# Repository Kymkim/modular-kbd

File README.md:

# MSKBD - Modularly Simple KeyBoarD

> [!WARNING]  
> This is under development. If you want the latest developments check out the `dev` branch.

A customizable modular keyboard system where each key cluster is its own module, connected through a grid-like commnication. The goal is to create a flexible keyboard that can scale, reconfigure layouts, and support hot-swapping modules.

## Features
- 🧩 **Modular design** — attach modules in any direction
- 🎛️ **Configurable firmware** — master + module code, easily updated
- ⚡ **Hotplug detection** — modules can be discovered dynamically

# Numpad Module

## Repo Structure
```
├─firmware/ - Embedded code for the core system
├─hardware/ - Schematics and PCB layouts
├─software/ - Host tools (keymap editor, etc.) (not yet implemented - soon hopefully!)
├─docs/ - Design notes, communication protocol, build guides
└─assets/ - Renders, diagrams, and media
```

## Branch Structure
```
main              # Stable, production-ready code (only tested & reviewed changes go here)
│
├─ dev            # Integration branch for features; "staging" area before merging to main
│  ├─ software-xxxxxx     # New features, experiments, improvements, or PCB uploads    
|  ├─ firmware-xxxxxx     # Please indicate in the branch the wether if its software
│  └─ hardware-xxxxxx     # firmware, or hardware
│
├─ hotfix/        # Quick fixes for urgent bugs in main
│   └─ hotfix/usb-detection
│
└─ docs/          # Documentation updates
    └─ docs/protocol-update
```

## Contributors

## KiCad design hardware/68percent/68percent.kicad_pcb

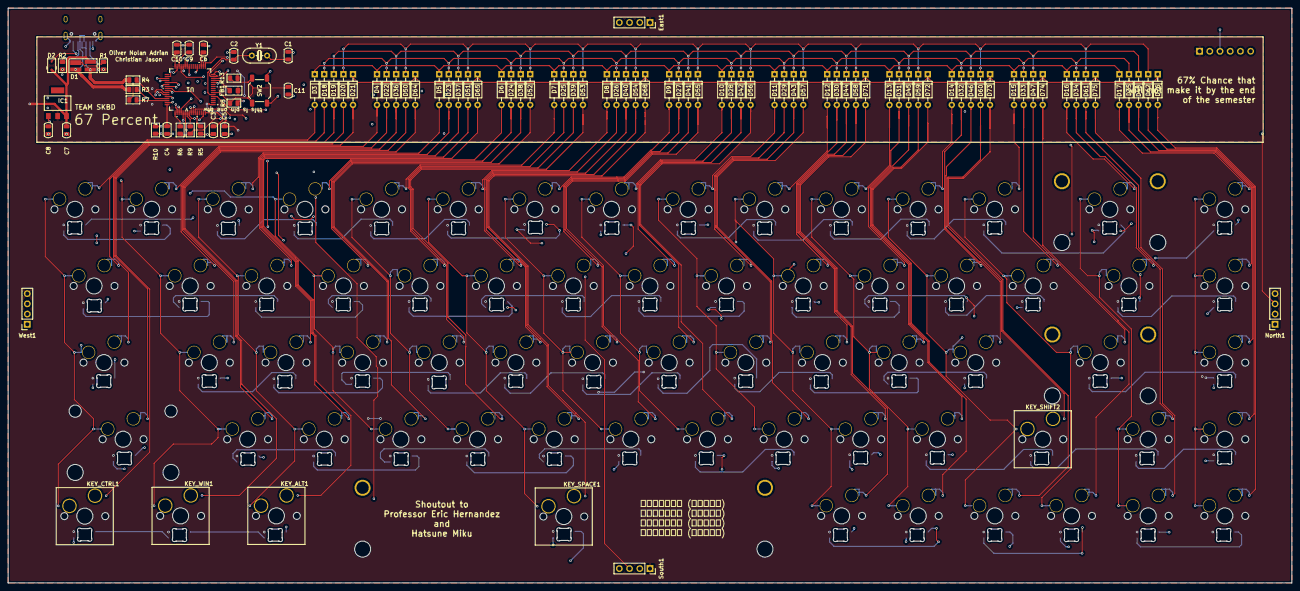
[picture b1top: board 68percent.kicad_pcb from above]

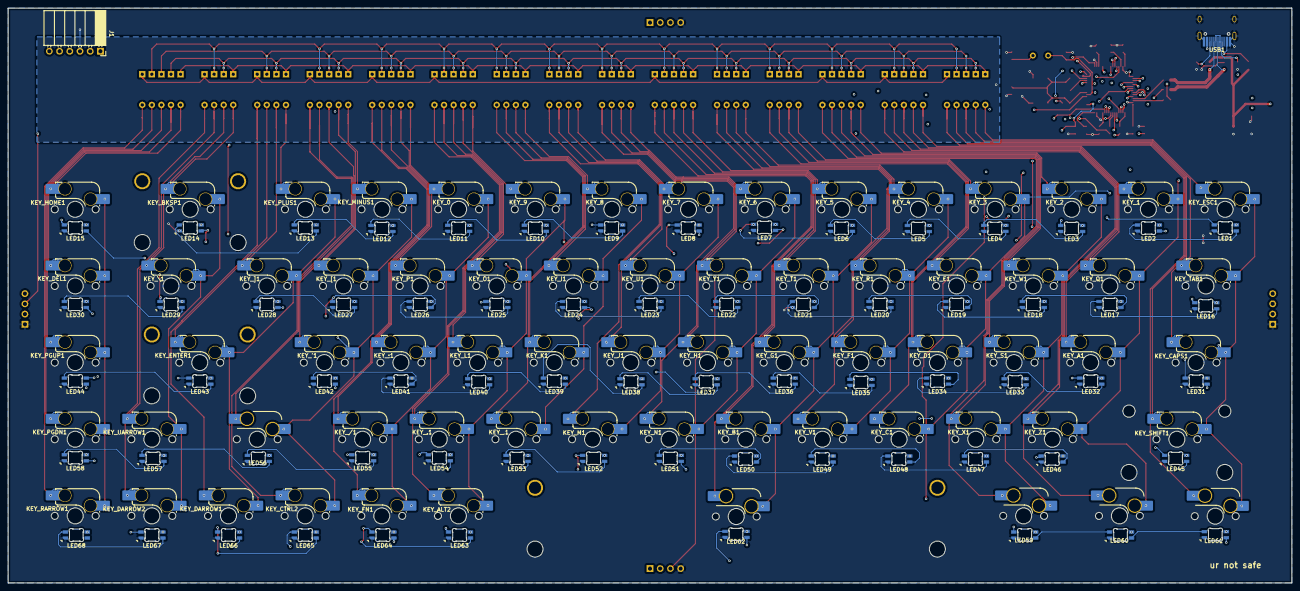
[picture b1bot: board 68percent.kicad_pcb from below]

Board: 4 copper layers, 319.1 x 142.9 mm, 243 parts (133 on the bottom side), 188 nets.

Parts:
C1, C2: 20pF; C_0805_2012Metric
C3, C4, C5, C6: 100nF; C_0805_2012Metric
C7, C10: 1uF; C_0805_2012Metric
C8: 10uF; C_0805_2012Metric
C9: 4.7uF; C_0805_2012Metric
C11: 0.1uF; C_0805_2012Metric
D1: PRTR5V0U2X; SOT-143_Handsoldering
D2: BAT60JFILM; D_SOD-323
D3, D4, D5, D6, D7, D8, D9, D10, D11, D12, D13, D14, D15, D16, D17, D18, D19, D20, D21, D22, D23, D24, D25, D26, D27, D28, D29, D30, D31, D32, D33, D34, D35, D36, D37, D38, D39, D40, D41, D42, D43, D44, D45, D46, D47, D48, D50, D51, D52, D53, D54, D55, D56, D57, D58, D59, D60, D61, D62, D64, D65, D68, D71, D72, D73, D74, D75, D76: 1N4148W; D_DO-35_P7.62mm_Horizontal
East1: Conn_01x04; PinSocket_1x04_P2.54mm_Vertical
FB1: Ferrite_Bead; Fuse_0805_2012Metric_Pad1.15x1.40mm_BigPads
IC1: TEAM SKBD; SOT223
J1: Conn_01x06; PinSocket_1x06_P2.54mm_Horizontal
KEY_0, KEY_1, KEY_2, KEY_3, KEY_4, KEY_5, KEY_6, KEY_7, KEY_8, KEY_9, KEY_.1: MX_SW_HS; SW_MX_HS_CPG151101S11_1u
KEY_'1: MX_SW_HS; SW_MX_HS_CPG151101S11_1u
KEY_,1: MX_SW_HS; SW_MX_HS_CPG151101S11_1u
KEY_/1: MX_SW_HS; SW_MX_HS_CPG151101S11_1u
KEY_;1: MX_SW_HS; SW_MX_HS_CPG151101S11_1u
KEY_A1: MX_SW_HS; SW_MX_HS_CPG151101S11_1u
KEY_ALT1: MX_SW_HS; SW_Hotswap_Kailh_MX_Plated_1.25u
KEY_ALT2: MX_SW_HS; SW_MX_HS_CPG151101S11_1u
KEY_B1: MX_SW_HS; SW_MX_HS_CPG151101S11_1u
KEY_BKSP1: MX_SW_HS; SW_MX_HS_CPG151101S11_1u
KEY_C1: MX_SW_HS; SW_MX_HS_CPG151101S11_1u
KEY_CAPS1: MX_SW_HS; SW_MX_HS_CPG151101S11_1u
KEY_CTRL1: MX_SW_HS; SW_Hotswap_Kailh_MX_Plated_1.25u
KEY_CTRL2: MX_SW_HS; SW_MX_HS_CPG151101S11_1u
KEY_D1: MX_SW_HS; SW_MX_HS_CPG151101S11_1u
KEY_DARROW1, KEY_DARROW2: MX_SW_HS; SW_MX_HS_CPG151101S11_1u
KEY_DEL1: MX_SW_HS; SW_MX_HS_CPG151101S11_1u
KEY_E1: MX_SW_HS; SW_MX_HS_CPG151101S11_1u
KEY_ENTER1: MX_SW_HS; SW_MX_HS_CPG151101S11_1u
KEY_ESC1: MX_SW_HS; SW_MX_HS_CPG151101S11_1u
KEY_F1: MX_SW_HS; SW_MX_HS_CPG151101S11_1u
KEY_FN1: MX_SW_HS; SW_MX_HS_CPG151101S11_1u
KEY_G1: MX_SW_HS; SW_MX_HS_CPG151101S11_1u
KEY_H1: MX_SW_HS; SW_MX_HS_CPG151101S11_1u
KEY_HOME1: MX_SW_HS; SW_MX_HS_CPG151101S11_1u
KEY_I1: MX_SW_HS; SW_MX_HS_CPG151101S11_1u
KEY_J1: MX_SW_HS; SW_MX_HS_CPG151101S11_1u
KEY_K1: MX_SW_HS; SW_MX_HS_CPG151101S11_1u
KEY_L1: MX_SW_HS; SW_MX_HS_CPG151101S11_1u
KEY_M1: MX_SW_HS; SW_MX_HS_CPG151101S11_1u
KEY_MINUS1: MX_SW_HS; SW_MX_HS_CPG151101S11_1u
KEY_N1: MX_SW_HS; SW_MX_HS_CPG151101S11_1u
KEY_O1: MX_SW_HS; SW_MX_HS_CPG151101S11_1u
KEY_P1: MX_SW_HS; SW_MX_HS_CPG151101S11_1u
KEY_PGDN1: MX_SW_HS; SW_MX_HS_CPG151101S11_1u
KEY_PGUP1: MX_SW_HS; SW_MX_HS_CPG151101S11_1u
KEY_PLUS1: MX_SW_HS; SW_MX_HS_CPG151101S11_1u
KEY_Q1: MX_SW_HS; SW_MX_HS_CPG151101S11_1u
KEY_R1: MX_SW_HS; SW_MX_HS_CPG151101S11_1u
KEY_RARROW1: MX_SW_HS; SW_MX_HS_CPG151101S11_1u
KEY_S1: MX_SW_HS; SW_MX_HS_CPG151101S11_1u
KEY_SHIFT1: MX_SW_HS; SW_MX_HS_CPG151101S11_1u
KEY_SHIFT2: MX_SW_HS; SW_Hotswap_Kailh_MX_Plated_1.75u
KEY_SPACE1: MX_SW_HS; SW_Hotswap_Kailh_MX_Plated_1.25u
KEY_T1: MX_SW_HS; SW_MX_HS_CPG151101S11_1u
KEY_TAB1: MX_SW_HS; SW_MX_HS_CPG151101S11_1u
KEY_U1: MX_SW_HS; SW_MX_HS_CPG151101S11_1u
KEY_UARROW1: MX_SW_HS; SW_MX_HS_CPG151101S11_1u
KEY_V1: MX_SW_HS; SW_MX_HS_CPG151101S11_1u
KEY_W1: MX_SW_HS; SW_MX_HS_CPG151101S11_1u
KEY_WIN1: MX_SW_HS; SW_Hotswap_Kailh_MX_Plated_1.25u
KEY_X1: MX_SW_HS; SW_MX_HS_CPG151101S11_1u
KEY_Y1: MX_SW_HS; SW_MX_HS_CPG151101S11_1u
KEY_Z1: MX_SW_HS; SW_MX_HS_CPG151101S11_1u
KEY_[1: MX_SW_HS; SW_MX_HS_CPG151101S11_1u
KEY_\1: MX_SW_HS; SW_MX_HS_CPG151101S11_1.5u
KEY_]1: MX_SW_HS; SW_MX_HS_CPG151101S11_1u
LED1, LED2, LED3, LED4, LED5, LED6, LED7, LED8, LED9, LED10, LED11, LED12, LED13, LED14, LED15, LED16, LED17, LED18, LED19, LED20, LED21, LED22, LED23, LED24, LED25, LED26, LED27, LED28, LED29, LED30, LED31, LED32, LED33, LED34, LED35, LED36, LED37, LED38, LED39, LED40, LED41, LED42, LED43, LED44, LED45, LED46, LED47, LED48, LED49, LED50, LED51, LED52, LED53, LED54, LED55, LED56, LED57, LED58, LED59, LED60, LED61, LED62, LED63, LED64, LED65, LED66, LED67, LED68: choc_SK6812MINI-E; LED_choc_6028R
North1: Conn_01x04; PinSocket_1x04_P2.54mm_Vertical
R1, R2: 5.1k; R_0805_2012Metric
R3, R4, R6, R7, R8, R9: 22; R_0805_2012Metric
R5: 10k; R_0805_2012Metric
R10, R13: DNP; R_0805_2012Metric
S1: MX_stab; STAB_MX_2.25u
S2: MX_stab; STAB_MX_P_6.25u
S3: MX_stab; STAB_MX_P_2u
S4: MX_stab; STAB_MX_P_2.25u
SW2: Push_Button; SW_SPST_SKQG_WithStem
South1: Conn_01x04; PinSocket_1x04_P2.54mm_Vertical
U1: LQFP64-10x10mm
USB1: HRO-TYPE-C-31-M-12; HRO-TYPE-C-31-M-12-HandSoldering
West1: Conn_01x04; PinSocket_1x04_P2.54mm_Vertical
Y1: 8MHz; Crystal_HC52-U_Vertical

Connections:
+3.3V: C3.1, C4.1, C5.1, C6.1, C8.2, C10.1, FB1.2, IC1.2 (OUT), J1.1, R13.2, U1.1 (VBAT), U1.19 (VDD), U1.32 (VDD), U1.48 (VDD), U1.64 (VDD)
+5V: C7.1, D1.4 (VP), D2.1 (K), East1.1, IC1.3 (IN), LED1.1 (VDD), LED2.1 (VDD), LED3.1 (VDD), LED4.1 (VDD), LED5.1 (VDD), LED6.1 (VDD), LED7.1 (VDD), LED8.1 (VDD), LED9.1 (VDD), LED10.1 (VDD), LED11.1 (VDD), LED12.1 (VDD), LED13.1 (VDD), LED14.1 (VDD), LED15.1 (VDD), LED16.1 (VDD), LED17.1 (VDD), LED18.1 (VDD), LED19.1 (VDD), LED20.1 (VDD), LED21.1 (VDD), LED22.1 (VDD), LED23.1 (VDD), LED24.1 (VDD), LED25.1 (VDD), LED26.1 (VDD), LED27.1 (VDD), LED28.1 (VDD), LED29.1 (VDD), LED30.1 (VDD), LED31.1 (VDD), LED32.1 (VDD), LED33.1 (VDD), LED34.1 (VDD), LED35.1 (VDD), LED36.1 (VDD), LED37.1 (VDD), LED38.1 (VDD), LED39.1 (VDD), LED40.1 (VDD), LED41.1 (VDD), LED42.1 (VDD), LED43.1 (VDD), LED44.1 (VDD), LED45.1 (VDD), LED46.1 (VDD), LED47.1 (VDD), LED48.1 (VDD), LED49.1 (VDD), LED50.1 (VDD), LED51.1 (VDD), LED52.1 (VDD), LED53.1 (VDD), LED54.1 (VDD), LED55.1 (VDD), LED56.1 (VDD), LED57.1 (VDD), LED58.1 (VDD), LED59.1 (VDD), LED60.1 (VDD), LED61.1 (VDD), LED62.1 (VDD), LED63.1 (VDD), LED64.1 (VDD), LED65.1 (VDD), LED66.1 (VDD), LED67.1 (VDD), LED68.1 (VDD), North1.4, South1.1, West1.4
/COL1: KEY_CAPS1.1, KEY_CTRL1.1, KEY_ESC1.1, KEY_SHIFT1.1, KEY_TAB1.1, U1.34 (PB13)
/COL2: KEY_1.1, KEY_A1.1, KEY_Q1.1, KEY_WIN1.1, KEY_Z1.1, U1.35 (PB14)
/COL3: KEY_2.1, KEY_ALT1.1, KEY_S1.1, KEY_W1.1, KEY_X1.1, U1.36 (PB15)
/COL4: KEY_3.1, KEY_C1.1, KEY_D1.1, KEY_E1.1, U1.37 (PC6)
/COL5: KEY_4.1, KEY_F1.1, KEY_R1.1, KEY_V1.1, U1.38 (PC7)
/COL6: KEY_5.1, KEY_B1.1, KEY_G1.1, KEY_SPACE1.1, KEY_T1.1, U1.39 (PC8)
/COL7: KEY_6.1, KEY_H1.1, KEY_N1.1, KEY_Y1.1, U1.40 (PC9)
/COL8: KEY_7.1, KEY_J1.1, KEY_M1.1, KEY_U1.1, U1.41 (PA8)
/COL9: KEY_8.1, KEY_,1.1, KEY_I1.1, KEY_K1.1, U1.50 (PA15)
/COL10: KEY_9.1, KEY_.1.1, KEY_ALT2.1, KEY_L1.1, KEY_O1.1, U1.51 (PA10)
/COL11: KEY_0.1, KEY_/1.1, KEY_;1.1, KEY_FN1.1, KEY_P1.1, U1.52 (PC11)
/COL12: KEY_'1.1, KEY_CTRL2.1, KEY_MINUS1.1, KEY_SHIFT2.1, KEY_[1.1, U1.56 (PB4)
/COL13: KEY_DARROW1.1, KEY_ENTER1.1, KEY_PLUS1.1, KEY_]1.1, U1.57 (PB5)
/COL14: KEY_BKSP1.1, KEY_DARROW2.1, KEY_UARROW1.1, KEY_\1.1, U1.58 (PB6)
/COL15: KEY_DEL1.1, KEY_HOME1.1, KEY_PGDN1.1, KEY_PGUP1.1, KEY_RARROW1.1, U1.59 (PB7)
/D+: D1.3 (L2), R4.1, USB1.6 (DP1), USB1.8 (DP2)
/D-: D1.2 (L1), R3.2, USB1.5 (DN2), USB1.7 (DN1)
/JTCLK: R6.2, U1.49 (PA14)
/JTMS: R7.2, U1.46 (PA13)
/NRST: C11.2, R8.1, R13.1, SW2.1, U1.7 (NRST)
/RGB_DATAIN: LED1.3 (DIN), U1.21 (PA5)
/ROW1: D3.1 (K), D4.1 (K), D5.1 (K), D6.1 (K), D7.1 (K), D8.1 (K), D9.1 (K), D10.1 (K), D11.1 (K), D12.1 (K), D13.1 (K), D14.1 (K), D15.1 (K), D16.1 (K), D17.1 (K), U1.29 (PB10)
/ROW2: D18.1 (K), D22.1 (K), D23.1 (K), D24.1 (K), D25.1 (K), D26.1 (K), D27.1 (K), D28.1 (K), D29.1 (K), D30.1 (K), D31.1 (K), D32.1 (K), D33.1 (K), D34.1 (K), D35.1 (K), U1.28 (PB2)
/ROW3: D19.1 (K), D36.1 (K), D37.1 (K), D38.1 (K), D39.1 (K), D40.1 (K), D41.1 (K), D42.1 (K), D43.1 (K), D44.1 (K), D45.1 (K), D46.1 (K), D47.1 (K), D48.1 (K), U1.27 (PB1)
/ROW4: D20.1 (K), D50.1 (K), D51.1 (K), D52.1 (K), D53.1 (K), D54.1 (K), D55.1 (K), D56.1 (K), D57.1 (K), D58.1 (K), D59.1 (K), D60.1 (K), D61.1 (K), D62.1 (K), U1.26 (PB0)
/ROW5: D21.1 (K), D64.1 (K), D65.1 (K), D68.1 (K), D71.1 (K), D72.1 (K), D73.1 (K), D74.1 (K), D75.1 (K), D76.1 (K), U1.25 (PC5)
/SWO: R9.2, U1.55 (PB3)
/UART_RX_EAST: East1.2, U1.14 (PA0)
/UART_RX_NORTH: North1.2, U1.17 (PA3)
/UART_RX_SOUTH: South1.2, U1.54 (PD2)
/UART_RX_WEST: U1.42 (PA9), West1.2
/UART_TX_EAST: East1.3, U1.15 (PA1)
/UART_TX_NORTH: North1.3, U1.16 (PA2)
/UART_TX_SOUTH: South1.3, U1.53 (PC12)
/UART_TX_WEST: U1.43 (PA10), West1.3
AGND: R10.1, U1.12 (VSSA)
GND: C1.2, C2.2, C3.2, C4.2, C5.2, C6.2, C7.2, C8.1, C9.1, C10.2, C11.1, D1.1 (VN), East1.4, IC1.1 (ADJ), J1.3, LED1.4 (VSS), LED2.4 (VSS), LED3.4 (VSS), LED4.4 (VSS), LED5.4 (VSS), LED6.4 (VSS), LED7.4 (VSS), LED8.4 (VSS), LED9.4 (VSS), LED10.4 (VSS), LED11.4 (VSS), LED12.4 (VSS), LED13.4 (VSS), LED14.4 (VSS), LED15.4 (VSS), LED16.4 (VSS), LED17.4 (VSS), LED18.4 (VSS), LED19.4 (VSS), LED20.4 (VSS), LED21.4 (VSS), LED22.4 (VSS), LED23.4 (VSS), LED24.4 (VSS), LED25.4 (VSS), LED26.4 (VSS), LED27.4 (VSS), LED28.4 (VSS), LED29.4 (VSS), LED30.4 (VSS), LED31.4 (VSS), LED32.4 (VSS), LED33.4 (VSS), LED34.4 (VSS), LED35.4 (VSS), LED36.4 (VSS), LED37.4 (VSS), LED38.4 (VSS), LED39.4 (VSS), LED40.4 (VSS), LED41.4 (VSS), LED42.4 (VSS), LED43.4 (VSS), LED44.4 (VSS), LED45.4 (VSS), LED46.4 (VSS), LED47.4 (VSS), LED48.4 (VSS), LED49.4 (VSS), LED50.4 (VSS), LED51.4 (VSS), LED52.4 (VSS), LED53.4 (VSS), LED54.4 (VSS), LED55.4 (VSS), LED56.4 (VSS), LED57.4 (VSS), LED58.4 (VSS), LED59.4 (VSS), LED60.4 (VSS), LED61.4 (VSS), LED62.4 (VSS), LED63.4 (VSS), LED64.4 (VSS), LED65.4 (VSS), LED66.4 (VSS), LED67.4 (VSS), LED68.4 (VSS), North1.1, R1.2, R2.2, R5.1, R10.2, SW2.2, South1.4, U1.18 (VSS), U1.31 (VSS), U1.47 (VSS), U1.63 (VSS), USB1.1 (GND), USB1.12 (GND), USB1.13 (SHIELD), West1.1
unnamed: D2.2 (A), USB1.2 (VBUS), USB1.11 (VBUS)
unnamed: D3.2 (A), KEY_ESC1.2
unnamed: D4.2 (A), KEY_1.2
unnamed: D5.2 (A), KEY_2.2
unnamed: D6.2 (A), KEY_3.2
unnamed: D7.2 (A), KEY_4.2
unnamed: D8.2 (A), KEY_5.2
unnamed: D9.2 (A), KEY_6.2
unnamed: D10.2 (A), KEY_7.2
unnamed: D11.2 (A), KEY_8.2
unnamed: D12.2 (A), KEY_9.2
unnamed: D13.2 (A), KEY_0.2
unnamed: D14.2 (A), KEY_MINUS1.2
unnamed: D15.2 (A), KEY_PLUS1.2
unnamed: D16.2 (A), KEY_BKSP1.2
unnamed: D17.2 (A), KEY_HOME1.2
unnamed: D18.2 (A), KEY_TAB1.2
unnamed: D19.2 (A), KEY_CAPS1.2
unnamed: D20.2 (A), KEY_SHIFT1.2
unnamed: D21.2 (A), KEY_CTRL1.2
unnamed: D22.2 (A), KEY_Q1.2
unnamed: D23.2 (A), KEY_W1.2
unnamed: D24.2 (A), KEY_E1.2
unnamed: D25.2 (A), KEY_R1.2
unnamed: D26.2 (A), KEY_T1.2
unnamed: D27.2 (A), KEY_Y1.2
unnamed: D28.2 (A), KEY_U1.2
unnamed: D29.2 (A), KEY_I1.2
unnamed: D30.2 (A), KEY_O1.2
unnamed: D31.2 (A), KEY_P1.2
unnamed: D32.2 (A), KEY_[1.2
unnamed: D33.2 (A), KEY_]1.2
unnamed: D34.2 (A), KEY_\1.2
unnamed: D35.2 (A), KEY_DEL1.2
unnamed: D36.2 (A), KEY_A1.2
unnamed: D37.2 (A), KEY_S1.2
unnamed: D38.2 (A), KEY_D1.2
unnamed: D39.2 (A), KEY_F1.2
unnamed: D40.2 (A), KEY_G1.2
unnamed: D41.2 (A), KEY_H1.2
unnamed: D42.2 (A), KEY_J1.2
unnamed: D43.2 (A), KEY_K1.2
unnamed: D44.2 (A), KEY_L1.2
unnamed: D45.2 (A), KEY_;1.2
unnamed: D46.2 (A), KEY_'1.2
unnamed: D47.2 (A), KEY_ENTER1.2
unnamed: D48.2 (A), KEY_PGUP1.2
unnamed: D50.2 (A), KEY_Z1.2
unnamed: D51.2 (A), KEY_X1.2
unnamed: D52.2 (A), KEY_C1.2
unnamed: D53.2 (A), KEY_V1.2
unnamed: D54.2 (A), KEY_B1.2
unnamed: D55.2 (A), KEY_N1.2
unnamed: D56.2 (A), KEY_M1.2
unnamed: D57.2 (A), KEY_,1.2
unnamed: D58.2 (A), KEY_.1.2
unnamed: D59.2 (A), KEY_/1.2
unnamed: D60.2 (A), KEY_SHIFT2.2
unnamed: D61.2 (A), KEY_UARROW1.2
unnamed: D62.2 (A), KEY_PGDN1.2
unnamed: D64.2 (A), KEY_WIN1.2
unnamed: D65.2 (A), KEY_ALT1.2
unnamed: D68.2 (A), KEY_SPACE1.2
unnamed: D71.2 (A), KEY_ALT2.2
unnamed: D72.2 (A), KEY_FN1.2
unnamed: D73.2 (A), KEY_CTRL2.2
unnamed: D74.2 (A), KEY_DARROW1.2
unnamed: D75.2 (A), KEY_DARROW2.2
unnamed: D76.2 (A), KEY_RARROW1.2
unnamed: J1.2, R6.1
unnamed: J1.4, R7.1
unnamed: J1.5, R8.2
unnamed: J1.6, R9.1
unnamed: LED1.2 (DOUT), LED2.3 (DIN)
unnamed: LED2.2 (DOUT), LED3.3 (DIN)
unnamed: LED3.2 (DOUT), LED4.3 (DIN)
unnamed: LED4.2 (DOUT), LED5.3 (DIN)
unnamed: LED5.2 (DOUT), LED6.3 (DIN)
unnamed: LED6.2 (DOUT), LED7.3 (DIN)
unnamed: LED7.2 (DOUT), LED8.3 (DIN)
unnamed: LED8.2 (DOUT), LED9.3 (DIN)
unnamed: LED9.2 (DOUT), LED10.3 (DIN)
unnamed: LED10.2 (DOUT), LED11.3 (DIN)
unnamed: LED11.2 (DOUT), LED12.3 (DIN)
unnamed: LED12.2 (DOUT), LED13.3 (DIN)
unnamed: LED13.2 (DOUT), LED14.3 (DIN)
unnamed: LED14.2 (DOUT), LED15.3 (DIN)
unnamed: LED15.2 (DOUT), LED16.3 (DIN)
unnamed: LED16.2 (DOUT), LED17.3 (DIN)
unnamed: LED17.2 (DOUT), LED18.3 (DIN)
unnamed: LED18.2 (DOUT), LED19.3 (DIN)
unnamed: LED19.2 (DOUT), LED20.3 (DIN)
unnamed: LED20.2 (DOUT), LED21.3 (DIN)
unnamed: LED21.2 (DOUT), LED22.3 (DIN)
unnamed: LED22.2 (DOUT), LED23.3 (DIN)
unnamed: LED23.2 (DOUT), LED24.3 (DIN)
unnamed: LED24.2 (DOUT), LED25.3 (DIN)
unnamed: LED25.2 (DOUT), LED26.3 (DIN)
unnamed: LED26.2 (DOUT), LED27.3 (DIN)
unnamed: LED27.2 (DOUT), LED28.3 (DIN)
unnamed: LED28.2 (DOUT), LED29.3 (DIN)
unnamed: LED29.2 (DOUT), LED30.3 (DIN)
unnamed: LED30.2 (DOUT), LED31.3 (DIN)
unnamed: LED31.2 (DOUT), LED32.3 (DIN)
unnamed: LED32.2 (DOUT), LED33.3 (DIN)
unnamed: LED33.2 (DOUT), LED34.3 (DIN)
unnamed: LED34.2 (DOUT), LED35.3 (DIN)
unnamed: LED35.2 (DOUT), LED36.3 (DIN)
unnamed: LED36.2 (DOUT), LED37.3 (DIN)
unnamed: LED37.2 (DOUT), LED38.3 (DIN)
unnamed: LED38.2 (DOUT), LED39.3 (DIN)
unnamed: LED39.2 (DOUT), LED40.3 (DIN)
unnamed: LED40.2 (DOUT), LED41.3 (DIN)
unnamed: LED41.2 (DOUT), LED42.3 (DIN)
unnamed: LED42.2 (DOUT), LED43.3 (DIN)
unnamed: LED43.2 (DOUT), LED44.3 (DIN)
unnamed: LED44.2 (DOUT), LED45.3 (DIN)
unnamed: LED45.2 (DOUT), LED46.3 (DIN)
unnamed: LED46.2 (DOUT), LED47.3 (DIN)
unnamed: LED47.2 (DOUT), LED48.3 (DIN)
unnamed: LED48.2 (DOUT), LED49.3 (DIN)
unnamed: LED49.2 (DOUT), LED50.3 (DIN)
unnamed: LED50.2 (DOUT), LED51.3 (DIN)
unnamed: LED51.2 (DOUT), LED52.3 (DIN)
unnamed: LED52.2 (DOUT), LED53.3 (DIN)
unnamed: LED53.2 (DOUT), LED54.3 (DIN)
unnamed: LED54.2 (DOUT), LED55.3 (DIN)
unnamed: LED55.2 (DOUT), LED56.3 (DIN)
unnamed: LED56.2 (DOUT), LED57.3 (DIN)
unnamed: LED57.2 (DOUT), LED58.3 (DIN)
unnamed: LED58.2 (DOUT), LED59.3 (DIN)
unnamed: LED59.2 (DOUT), LED60.3 (DIN)
unnamed: LED60.2 (DOUT), LED61.3 (DIN)
unnamed: LED61.2 (DOUT), LED62.3 (DIN)
unnamed: LED62.2 (DOUT), LED63.3 (DIN)
unnamed: LED63.2 (DOUT), LED64.3 (DIN)
unnamed: LED64.2 (DOUT), LED65.3 (DIN)
unnamed: LED65.2 (DOUT), LED66.3 (DIN)
unnamed: LED66.2 (DOUT), LED67.3 (DIN)
unnamed: LED67.2 (DOUT), LED68.3 (DIN)
unnamed: R5.2, U1.60 (BOOT)
unnamed: C1.1, U1.5 (OSCIN), Y1.2
unnamed: C2.1, U1.6 (OSCOUT), Y1.1
unnamed: R3.1, U1.44 (PA11)
unnamed: R4.2, U1.45 (PA12)
unnamed: C9.2, U1.30 (VCAP)
unnamed: FB1.1, U1.13 (VDDA)
unnamed: R2.1, USB1.4 (CC1)
unnamed: R1.1, USB1.10 (CC2)

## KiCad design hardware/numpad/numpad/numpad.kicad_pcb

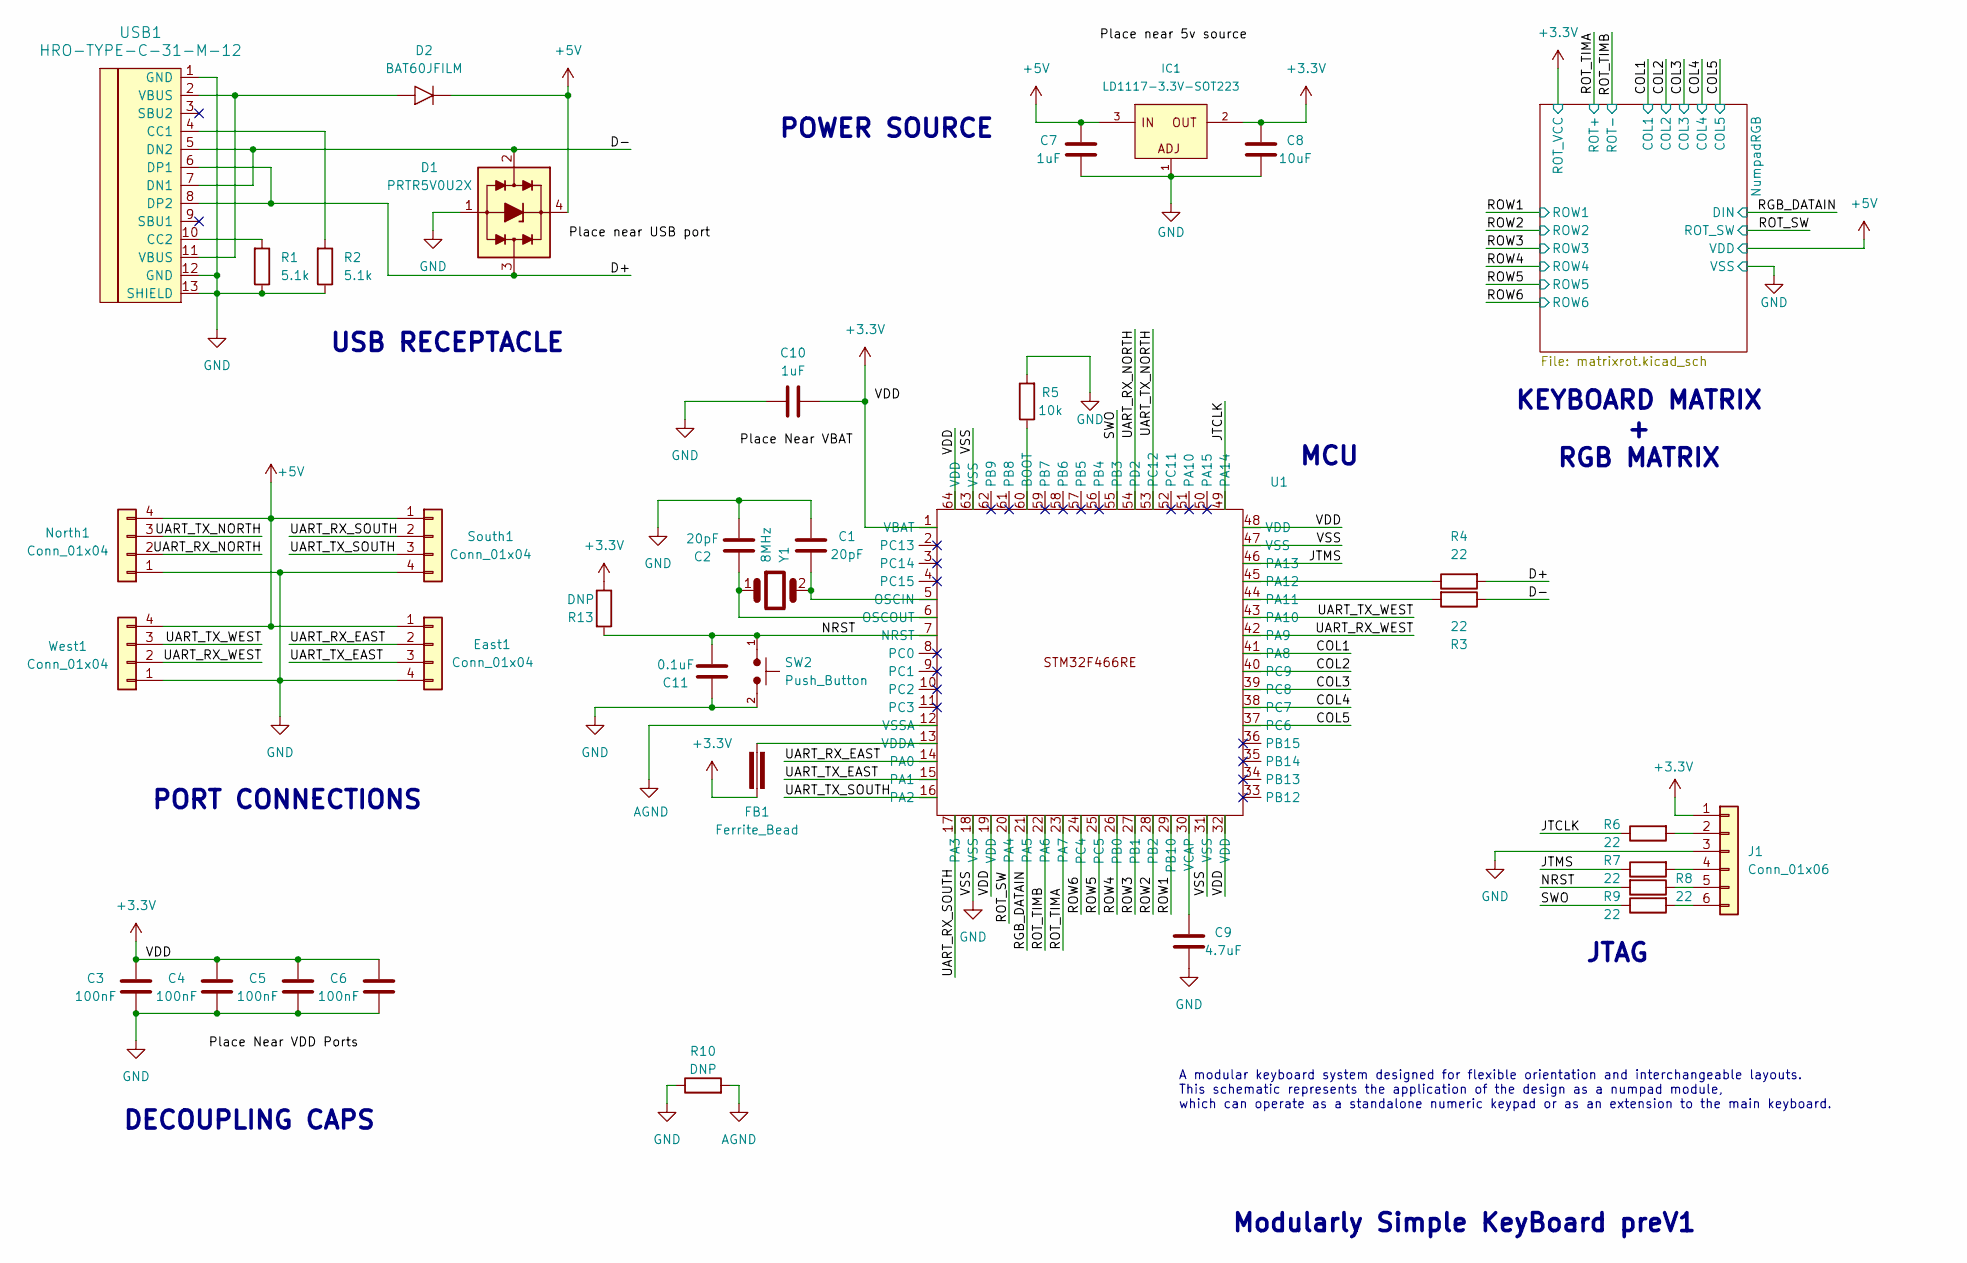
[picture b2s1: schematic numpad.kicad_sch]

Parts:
C1, C2: 20pF; C_0805_2012Metric
C3, C4, C5, C6: 100nF; C_0805_2012Metric
C7, C10: 1uF; C_0805_2012Metric
C8: 10uF; C_0805_2012Metric
C9: 4.7uF; C_0805_2012Metric
C11: 0.1uF; C_0805_2012Metric
D1: PRTR5V0U2X; SOT-143_Handsoldering
D2: BAT60JFILM; D_SOD-323
East1: Conn_01x04; PinSocket_1x04_P2.54mm_Vertical; Part Number 1-0401FBV0T
FB1: Ferrite_Bead; Fuse_0805_2012Metric_Pad1.15x1.40mm_BigPads
IC1: LD1117-3.3V-SOT223; SOT223; Part Number LD1117S33CTR
J1: Conn_01x06; PinSocket_1x06_P2.54mm_Horizontal; Part Number 1-0601FBV0T
North1: Conn_01x04; PinSocket_1x04_P2.54mm_Vertical; Part Number 1-0401FBV0T
R1, R2: 5.1k; R_0805_2012Metric
R3, R4, R6, R7, R8, R9: 22; R_0805_2012Metric
R5: 10k; R_0805_2012Metric
R10, R13: DNP; R_0805_2012Metric
SW2: Push_Button; SW_SPST_SKQG_WithStem
South1: Conn_01x04; PinSocket_1x04_P2.54mm_Vertical; Part Number 1-0401FBV0T
U1: LQFP64-10x10mm
USB1: HRO-TYPE-C-31-M-12; HRO-TYPE-C-31-M-12-HandSoldering
West1: Conn_01x04; PinSocket_1x04_P2.54mm_Vertical; Part Number 1-0401FBV0T
Y1: 8MHz; Crystal_HC52-U_Vertical

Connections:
+3.3V: C3.1, C4.1, C5.1, C6.1, C8.2, C10.1, FB1.2, IC1.2 (OUT), J1.1, R13.2, U1.1 (VBAT), U1.19 (VDD), U1.32 (VDD), U1.48 (VDD), U1.64 (VDD); also elsewhere on the board
+5V: C7.1, D1.4 (VP), D2.1 (K), East1.1, IC1.3 (IN), North1.4, South1.1, West1.4; also elsewhere on the board
/COL1: U1.41 (PA8); also elsewhere on the board
/COL2: U1.40 (PC9); also elsewhere on the board
/COL3: U1.39 (PC8); also elsewhere on the board
/COL4: U1.38 (PC7); also elsewhere on the board
/COL5: U1.37 (PC6); also elsewhere on the board
/D+: D1.3 (L2), R4.1, USB1.6 (DP1), USB1.8 (DP2)
/D-: D1.2 (L1), R3.2, USB1.5 (DN2), USB1.7 (DN1)
/JTCLK: R6.2, U1.49 (PA14)
/JTMS: R7.2, U1.46 (PA13)
/NRST: C11.2, R8.1, R13.1, SW2.1, U1.7 (NRST)
/RGB_DATAIN: U1.21 (PA5); also elsewhere on the board
/ROT_SW: U1.20 (PA4); also elsewhere on the board
/ROT_TIMA: U1.23 (PA7); also elsewhere on the board
/ROT_TIMB: U1.22 (PA6); also elsewhere on the board
/ROW1: U1.29 (PB10); also elsewhere on the board
/ROW2: U1.28 (PB2); also elsewhere on the board
/ROW3: U1.27 (PB1); also elsewhere on the board
/ROW4: U1.26 (PB0); also elsewhere on the board
/ROW5: U1.25 (PC5); also elsewhere on the board
/ROW6: U1.24 (PC4); also elsewhere on the board
/SWO: R9.2, U1.55 (PB3)
/UART_RX_EAST: East1.2, U1.14 (PA0)
/UART_RX_NORTH: North1.2, U1.54 (PD2)
/UART_RX_SOUTH: South1.2, U1.17 (PA3)
/UART_RX_WEST: U1.42 (PA9), West1.2
/UART_TX_EAST: East1.3, U1.15 (PA1)
/UART_TX_NORTH: North1.3, U1.53 (PC12)
/UART_TX_SOUTH: South1.3, U1.16 (PA2)
/UART_TX_WEST: U1.43 (PA10), West1.3
AGND: R10.1, U1.12 (VSSA)
GND: C1.2, C2.2, C3.2, C4.2, C5.2, C6.2, C7.2, C8.1, C9.1, C10.2, C11.1, D1.1 (VN), East1.4, IC1.1 (ADJ), J1.3, North1.1, R1.2, R2.2, R5.1, R10.2, SW2.2, South1.4, U1.18 (VSS), U1.31 (VSS), U1.47 (VSS), U1.63 (VSS), USB1.1 (GND), USB1.12 (GND), USB1.13 (SHIELD), West1.1; also elsewhere on the board
unnamed: D2.2 (A), USB1.2 (VBUS), USB1.11 (VBUS)
unnamed: J1.2, R6.1
unnamed: J1.4, R7.1
unnamed: J1.5, R8.2
unnamed: J1.6, R9.1
unnamed: R5.2, U1.60 (BOOT)
unnamed: C1.1, U1.5 (OSCIN), Y1.2
unnamed: C2.1, U1.6 (OSCOUT), Y1.1
unnamed: R3.1, U1.44 (PA11)
unnamed: R4.2, U1.45 (PA12)
unnamed: C9.2, U1.30 (VCAP)
unnamed: FB1.1, U1.13 (VDDA)
unnamed: R2.1, USB1.4 (CC1)
unnamed: R1.1, USB1.10 (CC2)

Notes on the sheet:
MCU
+ RGB MATRIX
DECOUPLING CAPS
PORT CONNECTIONS
POWER SOURCE
USB RECEPTACLE
KEYBOARD MATRIX
A modular keyboard system designed for flexible orientation and interchangeable layouts. This schematic represents the application of the design as a numpad module, which can operate as a standalone numeric keypad or as an extension to the main keyboard.
Modularly Simple KeyBoard preV1
JTAG

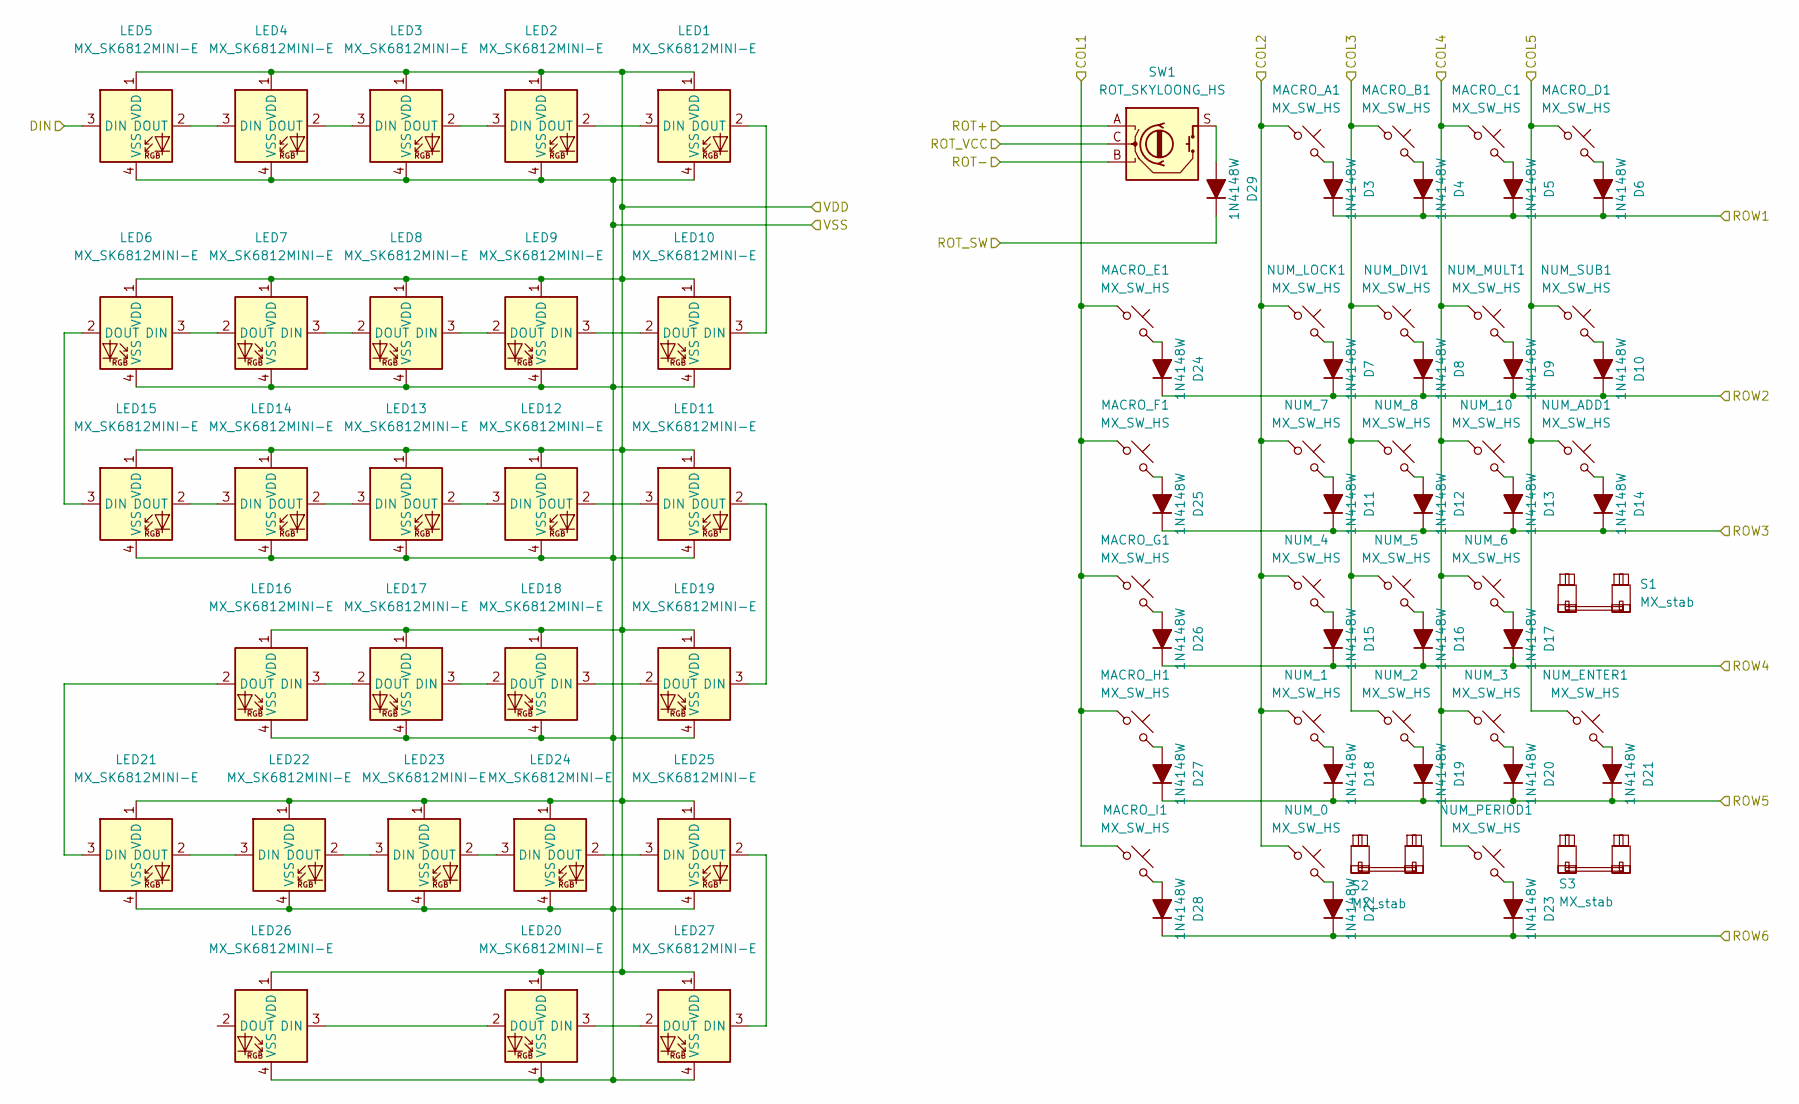
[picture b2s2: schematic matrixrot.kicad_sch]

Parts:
D3, D4, D5, D6, D7, D8, D9, D10, D11, D12, D13, D14, D15, D16, D17, D18, D19, D20, D21, D22, D23, D24, D25, D26, D27, D28, D29: 1N4148W; D_SOD-123
LED1, LED2, LED3, LED4, LED5, LED6, LED7, LED8, LED9, LED10, LED11, LED12, LED13, LED14, LED15, LED16, LED17, LED18, LED19, LED20, LED21, LED22, LED23, LED24, LED25, LED26, LED27: MX_SK6812MINI-E; LED_MX_6028R
MACRO_A1: MX_SW_HS; SW_MX_HS_CPG151101S11_1u
MACRO_B1: MX_SW_HS; SW_MX_HS_CPG151101S11_1u
MACRO_C1: MX_SW_HS; SW_MX_HS_CPG151101S11_1u
MACRO_D1: MX_SW_HS; SW_MX_HS_CPG151101S11_1u
MACRO_E1: MX_SW_HS; SW_MX_HS_CPG151101S11_1u
MACRO_F1: MX_SW_HS; SW_MX_HS_CPG151101S11_1u
MACRO_G1: MX_SW_HS; SW_MX_HS_CPG151101S11_1u
MACRO_H1: MX_SW_HS; SW_MX_HS_CPG151101S11_1u
MACRO_I1: MX_SW_HS; SW_MX_HS_CPG151101S11_1u
NUM_0, NUM_1, NUM_2, NUM_3, NUM_4, NUM_5, NUM_6, NUM_7, NUM_8, NUM_10: MX_SW_HS; SW_MX_HS_CPG151101S11_1u
NUM_ADD1: MX_SW_HS; SW_MX_HS_CPG151101S11_1u
NUM_DIV1: MX_SW_HS; SW_MX_HS_CPG151101S11_1u
NUM_ENTER1: MX_SW_HS; SW_MX_HS_CPG151101S11_1u
NUM_LOCK1: MX_SW_HS; SW_MX_HS_CPG151101S11_1u
NUM_MULT1: MX_SW_HS; SW_MX_HS_CPG151101S11_1u
NUM_PERIOD1: MX_SW_HS; SW_MX_HS_CPG151101S11_1u
NUM_SUB1: MX_SW_HS; SW_MX_HS_CPG151101S11_1u
S1, S2, S3: MX_stab; STAB_MX_P_2u
SW1: ROT_SKYLOONG_HS; ROT_SKYLOONG_HS-Switch

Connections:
+3.3V: SW1.C; also elsewhere on the board
+5V: LED1.1 (VDD), LED2.1 (VDD), LED3.1 (VDD), LED4.1 (VDD), LED5.1 (VDD), LED6.1 (VDD), LED7.1 (VDD), LED8.1 (VDD), LED9.1 (VDD), LED10.1 (VDD), LED11.1 (VDD), LED12.1 (VDD), LED13.1 (VDD), LED14.1 (VDD), LED15.1 (VDD), LED16.1 (VDD), LED17.1 (VDD), LED18.1 (VDD), LED19.1 (VDD), LED20.1 (VDD), LED21.1 (VDD), LED22.1 (VDD), LED23.1 (VDD), LED24.1 (VDD), LED25.1 (VDD), LED26.1 (VDD), LED27.1 (VDD); also elsewhere on the board
/COL1: MACRO_E1.1, MACRO_F1.1, MACRO_G1.1, MACRO_H1.1, MACRO_I1.1; also elsewhere on the board
/COL2: MACRO_A1.1, NUM_0.1, NUM_1.1, NUM_4.1, NUM_7.1, NUM_LOCK1.1; also elsewhere on the board
/COL3: MACRO_B1.1, NUM_2.1, NUM_5.1, NUM_8.1, NUM_DIV1.1; also elsewhere on the board
/COL4: MACRO_C1.1, NUM_3.1, NUM_6.1, NUM_10.1, NUM_MULT1.1, NUM_PERIOD1.1; also elsewhere on the board
/COL5: MACRO_D1.1, NUM_ADD1.1, NUM_ENTER1.1, NUM_SUB1.1; also elsewhere on the board
/RGB_DATAIN: LED5.3 (DIN); also elsewhere on the board
/ROT_SW: D29.1 (K); also elsewhere on the board
/ROT_TIMA: SW1.A; also elsewhere on the board
/ROT_TIMB: SW1.B; also elsewhere on the board
/ROW1: D3.1 (K), D4.1 (K), D5.1 (K), D6.1 (K); also elsewhere on the board
/ROW2: D7.1 (K), D8.1 (K), D9.1 (K), D10.1 (K), D24.1 (K); also elsewhere on the board
/ROW3: D11.1 (K), D12.1 (K), D13.1 (K), D14.1 (K), D25.1 (K); also elsewhere on the board
/ROW4: D15.1 (K), D16.1 (K), D17.1 (K), D26.1 (K); also elsewhere on the board
/ROW5: D18.1 (K), D19.1 (K), D20.1 (K), D21.1 (K), D27.1 (K); also elsewhere on the board
/ROW6: D22.1 (K), D23.1 (K), D28.1 (K); also elsewhere on the board
GND: LED1.4 (VSS), LED2.4 (VSS), LED3.4 (VSS), LED4.4 (VSS), LED5.4 (VSS), LED6.4 (VSS), LED7.4 (VSS), LED8.4 (VSS), LED9.4 (VSS), LED10.4 (VSS), LED11.4 (VSS), LED12.4 (VSS), LED13.4 (VSS), LED14.4 (VSS), LED15.4 (VSS), LED16.4 (VSS), LED17.4 (VSS), LED18.4 (VSS), LED19.4 (VSS), LED20.4 (VSS), LED21.4 (VSS), LED22.4 (VSS), LED23.4 (VSS), LED24.4 (VSS), LED25.4 (VSS), LED26.4 (VSS), LED27.4 (VSS); also elsewhere on the board
unnamed: D3.2 (A), MACRO_A1.2
unnamed: D4.2 (A), MACRO_B1.2
unnamed: D5.2 (A), MACRO_C1.2
unnamed: D6.2 (A), MACRO_D1.2
unnamed: D7.2 (A), NUM_LOCK1.2
unnamed: D8.2 (A), NUM_DIV1.2
unnamed: D9.2 (A), NUM_MULT1.2
unnamed: D10.2 (A), NUM_SUB1.2
unnamed: D11.2 (A), NUM_7.2
unnamed: D12.2 (A), NUM_8.2
unnamed: D13.2 (A), NUM_10.2
unnamed: D14.2 (A), NUM_ADD1.2
unnamed: D15.2 (A), NUM_4.2
unnamed: D16.2 (A), NUM_5.2
unnamed: D17.2 (A), NUM_6.2
unnamed: D18.2 (A), NUM_1.2
unnamed: D19.2 (A), NUM_2.2
unnamed: D20.2 (A), NUM_3.2
unnamed: D21.2 (A), NUM_ENTER1.2
unnamed: D22.2 (A), NUM_0.2
unnamed: D23.2 (A), NUM_PERIOD1.2
unnamed: D24.2 (A), MACRO_E1.2
unnamed: D25.2 (A), MACRO_F1.2
unnamed: D26.2 (A), MACRO_G1.2
unnamed: D27.2 (A), MACRO_H1.2
unnamed: D28.2 (A), MACRO_I1.2
unnamed: D29.2 (A), SW1.S
unnamed: LED1.3 (DIN), LED2.2 (DOUT)
unnamed: LED1.2 (DOUT), LED10.3 (DIN)
unnamed: LED2.3 (DIN), LED3.2 (DOUT)
unnamed: LED3.3 (DIN), LED4.2 (DOUT)
unnamed: LED4.3 (DIN), LED5.2 (DOUT)
unnamed: LED6.3 (DIN), LED7.2 (DOUT)
unnamed: LED7.3 (DIN), LED8.2 (DOUT)
unnamed: LED8.3 (DIN), LED9.2 (DOUT)
unnamed: LED9.3 (DIN), LED10.2 (DOUT)
unnamed: LED11.3 (DIN), LED12.2 (DOUT)
unnamed: LED11.2 (DOUT), LED19.3 (DIN)
unnamed: LED12.3 (DIN), LED13.2 (DOUT)
unnamed: LED13.3 (DIN), LED14.2 (DOUT)
unnamed: LED14.3 (DIN), LED15.2 (DOUT)
unnamed: LED6.2 (DOUT), LED15.3 (DIN)
unnamed: LED16.3 (DIN), LED17.2 (DOUT)
unnamed: LED16.2 (DOUT), LED21.3 (DIN)
unnamed: LED17.3 (DIN), LED18.2 (DOUT)
unnamed: LED18.3 (DIN), LED19.2 (DOUT)
unnamed: LED20.3 (DIN), LED27.2 (DOUT)
unnamed: LED20.2 (DOUT), LED26.3 (DIN)
unnamed: LED21.2 (DOUT), LED22.3 (DIN)
unnamed: LED22.2 (DOUT), LED23.3 (DIN)
unnamed: LED23.2 (DOUT), LED24.3 (DIN)
unnamed: LED24.2 (DOUT), LED25.3 (DIN)
unnamed: LED25.2 (DOUT), LED27.3 (DIN)
